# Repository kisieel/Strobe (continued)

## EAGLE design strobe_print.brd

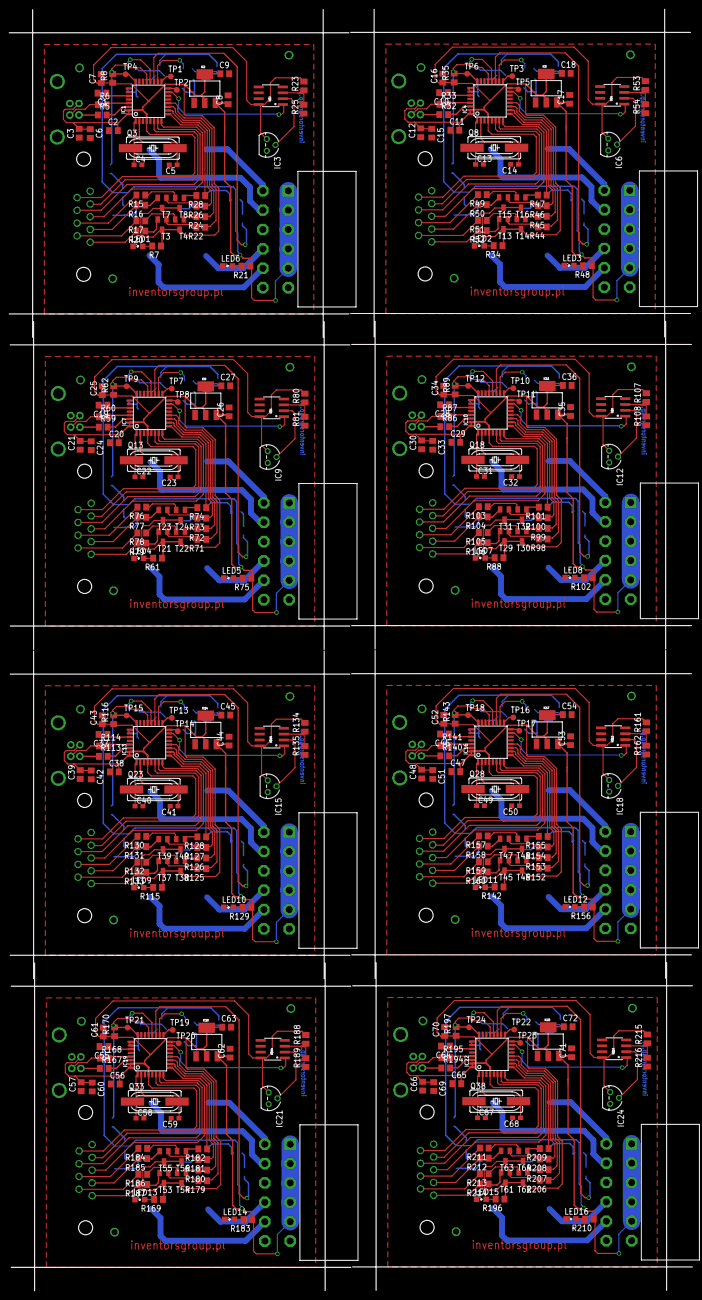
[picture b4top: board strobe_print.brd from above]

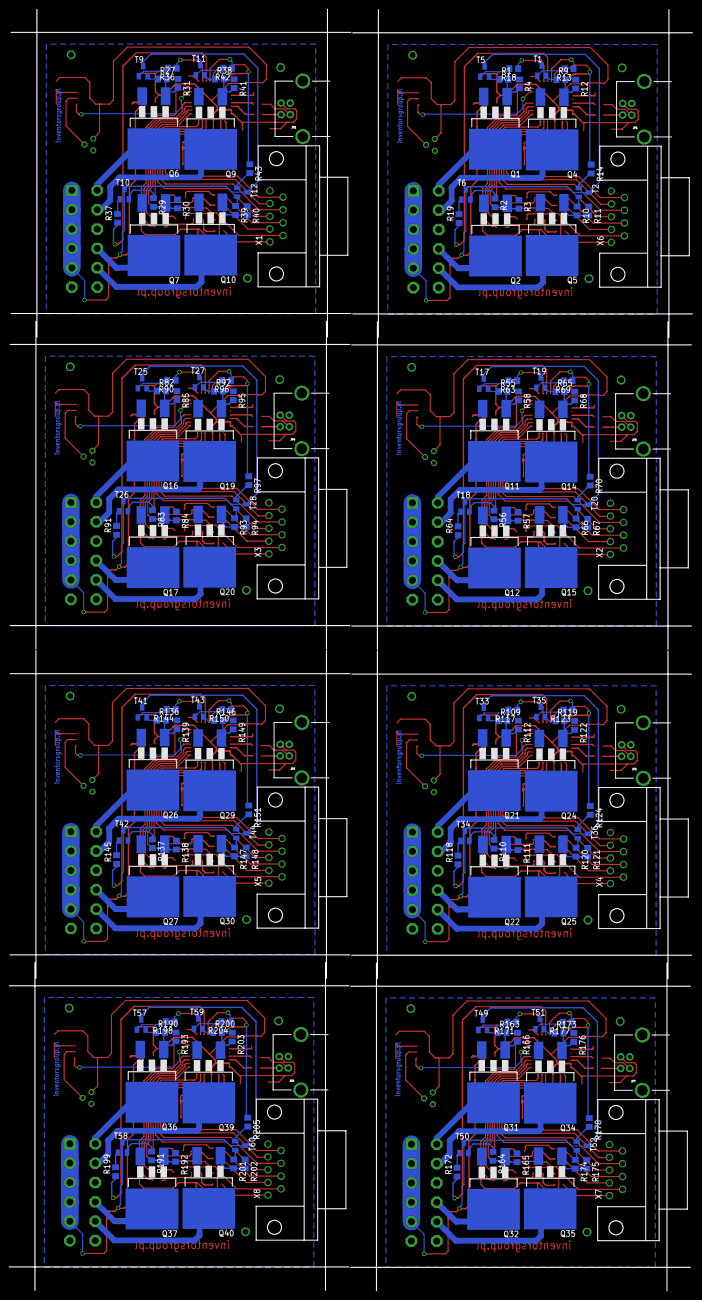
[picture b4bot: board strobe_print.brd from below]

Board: 2 copper layers, 148.1 x 277.9 mm, 488 parts (176 on the bottom side), 456 nets.

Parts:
C1, C10, C19, C28, C37, C46, C55, C64: 1uF; C0805
C2, C3, C6, C7, C8, C9, C11, C12, C15, C16, C17, C18, C20, C21, C24, C25, C26, C27, C29, C30, C33, C34, C35, C36, C38, C39, C42, C43, C44, C45, C47, C48, C51, C52, C53, C54, C56, C57, C60, C61, C62, C63, C65, C66, C69, C70, C71, C72: 100N; C0805
C4, C5, C13, C14, C22, C23, C31, C32, C40, C41, C49, C50, C58, C59, C67, C68: 22Pf; C0603
IC1, IC4, IC7, IC10, IC13, IC16, IC19, IC22: AT90USB162A; TQFP32-08
IC2, IC5, IC8, IC11, IC14, IC17, IC20, IC23: SOT223
IC3, IC6, IC9, IC12, IC15, IC18, IC21, IC24: LM35CZ; TO92
JP1, JP2, JP3, JP4, JP5, JP6, JP7, JP8: USB-B; USB-B-PTH
LED1, LED2, LED3, LED4, LED5, LED6, LED7, LED8, LED9, LED10, LED11, LED12, LED13, LED14, LED15, LED16: SML0805
Q1, Q2, Q4, Q5, Q6, Q7, Q9, Q10, Q11, Q12, Q14, Q15, Q16, Q17, Q19, Q20, Q21, Q22, Q24, Q25, Q26, Q27, Q29, Q30, Q31, Q32, Q34, Q35, Q36, Q37, Q39, Q40: IRF3704S; D2PACK
Q3, Q8, Q13, Q18, Q23, Q28, Q33, Q38: SM49
R1, R2, R3, R4, R9, R10, R11, R12, R13, R14, R15, R16, R17, R18, R19, R20, R22, R24, R26, R27, R28, R29, R30, R31, R36, R37, R38, R39, R40, R41, R42, R43, R44, R45, R46, R47, R49, R50, R51, R52, R55, R56, R57, R58, R63, R64, R65, R66, R67, R68, R69, R70, R71, R72, R73, R74, R76, R77, R78, R79, R82, R83, R84, R85, R90, R91, R92, R93, R94, R95, R96, R97, R98, R99, R100, R101, R103, R104, R105, R106, R109, R110, R111, R112, R117, R118, R119, R120, R121, R122, R123, R124, R125, R126, R127, R128, R130, R131, R132, R133, R136, R137, R138, R139, R144, R145, R146, R147, R148, R149, R150, R151, R152, R153, R154, R155, R157, R158, R159, R160, R163, R164, R165, R166, R171, R172, R173, R174, R175, R176, R177, R178, R179, R180, R181, R182, R184, R185, R186, R187, R190, R191, R192, R193, R198, R199, R200, R201, R202, R203, R204, R205, R206, R207, R208, R209, R211, R212, R213, R214: R0805
R5, R6, R32, R33, R59, R60, R86, R87, R113, R114, R140, R141, R167, R168, R194, R195: 22; R0805
R7, R21, R34, R48, R61, R75, R88, R102, R115, R129, R142, R156, R169, R183, R196, R210: 340; R0805
R8, R35, R62, R89, R116, R143, R170, R197: 10K; R0805
R23, R25, R53, R54, R80, R81, R107, R108, R134, R135, R161, R162, R188, R189, R215, R216: M0805
T1, T2, T3, T4, T5, T6, T7, T8, T9, T10, T11, T12, T13, T14, T15, T16, T17, T18, T19, T20, T21, T22, T23, T24, T25, T26, T27, T28, T29, T30, T31, T32, T33, T34, T35, T36, T37, T38, T39, T40, T41, T42, T43, T44, T45, T46, T47, T48, T49, T50, T51, T52, T53, T54, T55, T56, T57, T58, T59, T60, T61, T62, T63, T64: BC849; SOT23
TP1, TP2, TP3, TP4, TP5, TP6, TP7, TP8, TP9, TP10, TP11, TP12, TP13, TP14, TP15, TP16, TP17, TP18, TP19, TP20, TP21, TP22, TP23, TP24: TPB1,27; B1,27
U$1, U$3, U$5, U$7, U$9, U$11, U$13, U$15: MF42-10
U$2, U$4, U$6, U$8, U$10, U$12, U$14, U$16: LM393; SO08
X1, X2, X3, X4, X5, X6, X7, X8: D-SUB9-H3M09RA; H3M09RA

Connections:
5V: C2.2, C3.2, C6.1, C7.1, C9.1, IC1.4, IC1.31, IC1.32, IC2.2, IC2.4, IC3.1, JP1.VBUS, R7.1, R8.1, R23.2, T3.3, T4.3, T7.3, T8.3, U$2.8, X6.9
5V1: C11.2, C12.2, C15.1, C16.1, C18.1, IC4.4, IC4.31, IC4.32, IC5.2, IC5.4, IC6.1, JP2.VBUS, R34.1, R35.1, R53.2, T13.3, T14.3, T15.3, T16.3, U$4.8, X1.9
5V2: C20.2, C21.2, C24.1, C25.1, C27.1, IC7.4, IC7.31, IC7.32, IC8.2, IC8.4, IC9.1, JP3.VBUS, R61.1, R62.1, R80.2, T21.3, T22.3, T23.3, T24.3, U$6.8, X2.9
5V3: C29.2, C30.2, C33.1, C34.1, C36.1, IC10.4, IC10.31, IC10.32, IC11.2, IC11.4, IC12.1, JP4.VBUS, R88.1, R89.1, R107.2, T29.3, T30.3, T31.3, T32.3, U$8.8, X3.9
5V4: C38.2, C39.2, C42.1, C43.1, C45.1, IC13.4, IC13.31, IC13.32, IC14.2, IC14.4, IC15.1, JP5.VBUS, R115.1, R116.1, R134.2, T37.3, T38.3, T39.3, T40.3, U$10.8, X4.9
5V5: C47.2, C48.2, C51.1, C52.1, C54.1, IC16.4, IC16.31, IC16.32, IC17.2, IC17.4, IC18.1, JP6.VBUS, R142.1, R143.1, R161.2, T45.3, T46.3, T47.3, T48.3, U$12.8, X5.9
5V6: C56.2, C57.2, C60.1, C61.1, C63.1, IC19.4, IC19.31, IC19.32, IC20.2, IC20.4, IC21.1, JP7.VBUS, R169.1, R170.1, R188.2, T53.3, T54.3, T55.3, T56.3, U$14.8, X7.9
5V7: C65.2, C66.2, C69.1, C70.1, C72.1, IC22.4, IC22.31, IC22.32, IC23.2, IC23.4, IC24.1, JP8.VBUS, R196.1, R197.1, R215.2, T61.3, T62.3, T63.3, T64.3, U$16.8, X8.9
12V: C8.1, IC2.3, R21.1, T1.3, T2.3, T5.3, T6.3, U$1.1, U$1.2, U$1.3, U$1.4, U$1.5
12V1: C17.1, IC5.3, R48.1, T9.3, T10.3, T11.3, T12.3, U$3.1, U$3.2, U$3.3, U$3.4, U$3.5
12V2: C26.1, IC8.3, R75.1, T17.3, T18.3, T19.3, T20.3, U$5.1, U$5.2, U$5.3, U$5.4, U$5.5
12V3: C35.1, IC11.3, R102.1, T25.3, T26.3, T27.3, T28.3, U$7.1, U$7.2, U$7.3, U$7.4, U$7.5
12V4: C44.1, IC14.3, R129.1, T33.3, T34.3, T35.3, T36.3, U$9.1, U$9.2, U$9.3, U$9.4, U$9.5
12V5: C53.1, IC17.3, R156.1, T41.3, T42.3, T43.3, T44.3, U$11.1, U$11.2, U$11.3, U$11.4, U$11.5
12V6: C62.1, IC20.3, R183.1, T49.3, T50.3, T51.3, T52.3, U$13.1, U$13.2, U$13.3, U$13.4, U$13.5
12V7: C71.1, IC23.3, R210.1, T57.3, T58.3, T59.3, T60.3, U$15.1, U$15.2, U$15.3, U$15.4, U$15.5
B1: IC1.6, X6.4
B2: IC1.7, X6.8
B3: IC1.8, X6.3
B4: IC4.6, X1.4
B5: IC4.7, X1.8
B6: IC4.8, X1.3
B7: IC7.6, X2.4
B8: IC7.7, X2.8
B9: IC7.8, X2.3
B10: IC10.6, X3.4
B11: IC10.7, X3.8
B12: IC10.8, X3.3
B13: IC13.6, X4.4
B14: IC13.7, X4.8
B15: IC13.8, X4.3
B16: IC16.6, X5.4
B17: IC16.7, X5.8
B18: IC16.8, X5.3
B19: IC19.6, X7.4
B20: IC19.7, X7.8
B21: IC19.8, X7.3
B22: IC22.6, X8.4
B23: IC22.7, X8.8
B24: IC22.8, X8.3
CH1: IC1.18, R18.1
CH2: IC1.19, R19.1
CH3: IC1.20, R13.1
CH4: IC1.21, R14.1
CH5: IC4.18, R36.1
CH6: IC4.19, R37.1
CH7: IC4.20, R42.1
CH8: IC4.21, R43.1
CH9: IC7.18, R63.1
CH10: IC7.19, R64.1
CH11: IC7.20, R69.1
CH12: IC7.21, R70.1
CH13: IC10.18, R90.1
CH14: IC10.19, R91.1
CH15: IC10.20, R96.1
CH16: IC10.21, R97.1
CH17: IC13.18, R117.1
CH18: IC13.19, R118.1
CH19: IC13.20, R123.1
CH20: IC13.21, R124.1
CH21: IC16.18, R144.1
CH22: IC16.19, R145.1
CH23: IC16.20, R150.1
CH24: IC16.21, R151.1
CH25: IC19.18, R171.1
CH26: IC19.19, R172.1
CH27: IC19.20, R177.1
CH28: IC19.21, R178.1
CH29: IC22.18, R198.1
CH30: IC22.19, R199.1
CH31: IC22.20, R204.1
CH32: IC22.21, R205.1
GND: C1.2, C2.1, C3.1, C4.2, C5.2, C6.2, C7.2, C8.2, C9.2, IC1.3, IC1.28, IC2.1, IC3.3, JP1.GND, LED1.C, LED6.C, Q1.3, Q2.3, Q4.3, Q5.3, R3.1, R4.1, R11.1, R12.1, R25.1, U$1.8, U$1.11, U$1.12, U$2.4, X6.5
GND1: C10.2, C11.1, C12.1, C13.2, C14.2, C15.2, C16.2, C17.2, C18.2, IC4.3, IC4.28, IC5.1, IC6.3, JP2.GND, LED2.C, LED3.C, Q6.3, Q7.3, Q9.3, Q10.3, R30.1, R31.1, R40.1, R41.1, R54.1, U$3.8, U$3.11, U$3.12, U$4.4, X1.5
GND2: C19.2, C20.1, C21.1, C22.2, C23.2, C24.2, C25.2, C26.2, C27.2, IC7.3, IC7.28, IC8.1, IC9.3, JP3.GND, LED4.C, LED5.C, Q11.3, Q12.3, Q14.3, Q15.3, R57.1, R58.1, R67.1, R68.1, R81.1, U$5.8, U$5.11, U$5.12, U$6.4, X2.5
GND3: C28.2, C29.1, C30.1, C31.2, C32.2, C33.2, C34.2, C35.2, C36.2, IC10.3, IC10.28, IC11.1, IC12.3, JP4.GND, LED7.C, LED8.C, Q16.3, Q17.3, Q19.3, Q20.3, R84.1, R85.1, R94.1, R95.1, R108.1, U$7.8, U$7.11, U$7.12, U$8.4, X3.5
GND4: C37.2, C38.1, C39.1, C40.2, C41.2, C42.2, C43.2, C44.2, C45.2, IC13.3, IC13.28, IC14.1, IC15.3, JP5.GND, LED9.C, LED10.C, Q21.3, Q22.3, Q24.3, Q25.3, R111.1, R112.1, R121.1, R122.1, R135.1, U$9.8, U$9.11, U$9.12, U$10.4, X4.5
GND5: C46.2, C47.1, C48.1, C49.2, C50.2, C51.2, C52.2, C53.2, C54.2, IC16.3, IC16.28, IC17.1, IC18.3, JP6.GND, LED11.C, LED12.C, Q26.3, Q27.3, Q29.3, Q30.3, R138.1, R139.1, R148.1, R149.1, R162.1, U$11.8, U$11.11, U$11.12, U$12.4, X5.5
GND6: C55.2, C56.1, C57.1, C58.2, C59.2, C60.2, C61.2, C62.2, C63.2, IC19.3, IC19.28, IC20.1, IC21.3, JP7.GND, LED13.C, LED14.C, Q31.3, Q32.3, Q34.3, Q35.3, R165.1, R166.1, R175.1, R176.1, R189.1, U$13.8, U$13.11, U$13.12, U$14.4, X7.5
GND7: C64.2, C65.1, C66.1, C67.2, C68.2, C69.2, C70.2, C71.2, C72.2, IC22.3, IC22.28, IC23.1, IC24.3, JP8.GND, LED15.C, LED16.C, Q36.3, Q37.3, Q39.3, Q40.3, R192.1, R193.1, R202.1, R203.1, R216.1, U$15.8, U$15.11, U$15.12, U$16.4, X8.5
L1: Q1.2, U$1.6
L2: Q2.2, U$1.9
L3: Q4.2, U$1.7
L4: Q5.2, U$1.10
L5: Q6.2, U$3.6
L6: Q7.2, U$3.9
L7: Q9.2, U$3.7
L8: Q10.2, U$3.10
L9: Q11.2, U$5.6
L10: Q12.2, U$5.9
L11: Q14.2, U$5.7
L12: Q15.2, U$5.10
L13: Q16.2, U$7.6
L14: Q17.2, U$7.9
L15: Q19.2, U$7.7
L16: Q20.2, U$7.10
L17: Q21.2, U$9.6
L18: Q22.2, U$9.9
L19: Q24.2, U$9.7
L20: Q25.2, U$9.10
L21: Q26.2, U$11.6
L22: Q27.2, U$11.9
L23: Q29.2, U$11.7
L24: Q30.2, U$11.10
L25: Q31.2, U$13.6
L26: Q32.2, U$13.9
L27: Q34.2, U$13.7
L28: Q35.2, U$13.10
L29: Q36.2, U$15.6
L30: Q37.2, U$15.9
L31: Q39.2, U$15.7
L32: Q40.2, U$15.10
unnamed: Q1.1, R1.2, R4.2
unnamed: Q2.1, R2.2, R3.2
unnamed: IC3.2, U$2.2
unnamed: R23.1, R25.2, U$2.3
unnamed: C1.1, IC1.27
unnamed: JP1.D+, R6.1
unnamed: JP1.D-, R5.1
unnamed: IC1.30, R5.2
unnamed: IC1.29, R6.2
unnamed: LED1.A, R7.2
unnamed: Q4.1, R9.2, R12.2
unnamed: C5.1, IC1.2, Q3.2
unnamed: C4.1, IC1.1, Q3.1
unnamed: IC1.24, R8.2, TP4.TP
unnamed: Q5.1, R10.2, R11.2
unnamed: Q6.1, R27.2, R31.2
unnamed: Q7.1, R29.2, R30.2
unnamed: R9.1, T1.2
unnamed: R10.1, T2.2
unnamed: R13.2, T1.1
unnamed: R14.2, T2.1
unnamed: IC1.17, TP1.TP
unnamed: LED6.A, R21.2
unnamed: R22.2, T3.1
unnamed: IC1.16, TP2.TP
unnamed: R20.2, X6.1
unnamed: R24.2, T4.1
unnamed: R1.1, T5.2
unnamed: R2.1, T6.2
unnamed: R18.2, T5.1
unnamed: R19.2, T6.1
unnamed: C10.1, IC4.27
unnamed: R17.2, X6.6
unnamed: R26.2, T7.1
unnamed: R16.2, X6.2
unnamed: R15.2, X6.7
unnamed: R28.2, T8.1
unnamed: JP2.D+, R33.1
unnamed: JP2.D-, R32.1
unnamed: IC4.30, R32.2
unnamed: IC4.29, R33.2
unnamed: LED2.A, R34.2
unnamed: C14.1, IC4.2, Q8.2
unnamed: C13.1, IC4.1, Q8.1
unnamed: IC4.24, R35.2, TP6.TP
unnamed: R27.1, T9.2
unnamed: R29.1, T10.2
unnamed: R36.2, T9.1
unnamed: R37.2, T10.1
unnamed: Q9.1, R38.2, R41.2
unnamed: Q10.1, R39.2, R40.2
unnamed: R38.1, T11.2
unnamed: R39.1, T12.2
unnamed: R42.2, T11.1
unnamed: R43.2, T12.1
unnamed: R44.2, T13.1
unnamed: R45.2, T14.1
unnamed: R46.2, T15.1
unnamed: R47.2, T16.1
unnamed: IC4.17, TP3.TP
unnamed: IC4.16, TP5.TP
unnamed: LED3.A, R48.2
unnamed: R52.2, X1.1
unnamed: R51.2, X1.6
unnamed: R50.2, X1.2
unnamed: R49.2, X1.7
unnamed: IC6.2, U$4.2
unnamed: R53.1, R54.2, U$4.3
unnamed: Q11.1, R55.2, R58.2
unnamed: Q12.1, R56.2, R57.2
unnamed: C19.1, IC7.27
unnamed: JP3.D+, R60.1
unnamed: JP3.D-, R59.1
unnamed: IC7.30, R59.2
unnamed: IC7.29, R60.2
unnamed: LED4.A, R61.2
unnamed: C23.1, IC7.2, Q13.2
unnamed: C22.1, IC7.1, Q13.1
unnamed: IC7.24, R62.2, TP9.TP
unnamed: R55.1, T17.2
unnamed: R56.1, T18.2
unnamed: R63.2, T17.1
unnamed: R64.2, T18.1
unnamed: Q14.1, R65.2, R68.2
unnamed: Q15.1, R66.2, R67.2
unnamed: R65.1, T19.2
unnamed: R66.1, T20.2
unnamed: R69.2, T19.1
unnamed: R70.2, T20.1
unnamed: R71.2, T21.1
unnamed: R72.2, T22.1
unnamed: R73.2, T23.1
unnamed: R74.2, T24.1
unnamed: IC7.17, TP7.TP
unnamed: IC7.16, TP8.TP
unnamed: LED5.A, R75.2
unnamed: R79.2, X2.1
unnamed: R78.2, X2.6
unnamed: R77.2, X2.2
unnamed: R76.2, X2.7
unnamed: IC9.2, U$6.2
unnamed: R80.1, R81.2, U$6.3
unnamed: Q16.1, R82.2, R85.2
unnamed: Q17.1, R83.2, R84.2
unnamed: C28.1, IC10.27
unnamed: JP4.D+, R87.1
unnamed: JP4.D-, R86.1
unnamed: IC10.30, R86.2
unnamed: IC10.29, R87.2
unnamed: LED7.A, R88.2
unnamed: C32.1, IC10.2, Q18.2
unnamed: C31.1, IC10.1, Q18.1
unnamed: IC10.24, R89.2, TP12.TP
unnamed: R82.1, T25.2
unnamed: R83.1, T26.2
unnamed: R90.2, T25.1
unnamed: R91.2, T26.1
unnamed: Q19.1, R92.2, R95.2
unnamed: Q20.1, R93.2, R94.2
unnamed: R92.1, T27.2
unnamed: R93.1, T28.2
unnamed: R96.2, T27.1
unnamed: R97.2, T28.1
unnamed: R98.2, T29.1
unnamed: R99.2, T30.1
unnamed: R100.2, T31.1
unnamed: R101.2, T32.1
unnamed: IC10.17, TP10.TP
unnamed: IC10.16, TP11.TP
unnamed: LED8.A, R102.2
unnamed: R106.2, X3.1
unnamed: R105.2, X3.6
unnamed: R104.2, X3.2
unnamed: R103.2, X3.7
unnamed: IC12.2, U$8.2
unnamed: R107.1, R108.2, U$8.3
unnamed: Q21.1, R109.2, R112.2
unnamed: Q22.1, R110.2, R111.2
unnamed: C37.1, IC13.27
unnamed: JP5.D+, R114.1
unnamed: JP5.D-, R113.1
unnamed: IC13.30, R113.2
unnamed: IC13.29, R114.2
unnamed: LED9.A, R115.2
unnamed: C41.1, IC13.2, Q23.2
unnamed: C40.1, IC13.1, Q23.1
unnamed: IC13.24, R116.2, TP15.TP
unnamed: R109.1, T33.2
unnamed: R110.1, T34.2
unnamed: R117.2, T33.1
unnamed: R118.2, T34.1
unnamed: Q24.1, R119.2, R122.2
unnamed: Q25.1, R120.2, R121.2
unnamed: R119.1, T35.2
unnamed: R120.1, T36.2
unnamed: R123.2, T35.1
unnamed: R124.2, T36.1
unnamed: R125.2, T37.1
unnamed: R126.2, T38.1
unnamed: R127.2, T39.1
unnamed: R128.2, T40.1
unnamed: IC13.17, TP13.TP
unnamed: IC13.16, TP14.TP
unnamed: LED10.A, R129.2
unnamed: R133.2, X4.1
unnamed: R132.2, X4.6
unnamed: R131.2, X4.2
unnamed: R130.2, X4.7
unnamed: IC15.2, U$10.2
unnamed: R134.1, R135.2, U$10.3
unnamed: Q26.1, R136.2, R139.2
unnamed: Q27.1, R137.2, R138.2
unnamed: C46.1, IC16.27
unnamed: JP6.D+, R141.1
unnamed: JP6.D-, R140.1
unnamed: IC16.30, R140.2
unnamed: IC16.29, R141.2
unnamed: LED11.A, R142.2
unnamed: C50.1, IC16.2, Q28.2
unnamed: C49.1, IC16.1, Q28.1
unnamed: IC16.24, R143.2, TP18.TP
unnamed: R136.1, T41.2
unnamed: R137.1, T42.2
unnamed: R144.2, T41.1
unnamed: R145.2, T42.1
unnamed: Q29.1, R146.2, R149.2
unnamed: Q30.1, R147.2, R148.2
unnamed: R146.1, T43.2
unnamed: R147.1, T44.2
unnamed: R150.2, T43.1
unnamed: R151.2, T44.1
unnamed: R152.2, T45.1
unnamed: R153.2, T46.1
unnamed: R154.2, T47.1
unnamed: R155.2, T48.1
unnamed: IC16.17, TP16.TP
unnamed: IC16.16, TP17.TP
unnamed: LED12.A, R156.2
unnamed: R160.2, X5.1
unnamed: R159.2, X5.6
unnamed: R158.2, X5.2
unnamed: R157.2, X5.7
unnamed: IC18.2, U$12.2
unnamed: R161.1, R162.2, U$12.3
unnamed: Q31.1, R163.2, R166.2
unnamed: Q32.1, R164.2, R165.2
unnamed: C55.1, IC19.27
unnamed: JP7.D+, R168.1
unnamed: JP7.D-, R167.1
unnamed: IC19.30, R167.2
unnamed: IC19.29, R168.2
unnamed: LED13.A, R169.2
unnamed: C59.1, IC19.2, Q33.2
unnamed: C58.1, IC19.1, Q33.1
unnamed: IC19.24, R170.2, TP21.TP
unnamed: R163.1, T49.2
unnamed: R164.1, T50.2
unnamed: R171.2, T49.1
unnamed: R172.2, T50.1
unnamed: Q34.1, R173.2, R176.2
unnamed: Q35.1, R174.2, R175.2
unnamed: R173.1, T51.2
unnamed: R174.1, T52.2
unnamed: R177.2, T51.1
unnamed: R178.2, T52.1
unnamed: R179.2, T53.1
unnamed: R180.2, T54.1
unnamed: R181.2, T55.1
unnamed: R182.2, T56.1
unnamed: IC19.17, TP19.TP
unnamed: IC19.16, TP20.TP
unnamed: LED14.A, R183.2
unnamed: R187.2, X7.1
unnamed: R186.2, X7.6
unnamed: R185.2, X7.2
unnamed: R184.2, X7.7
unnamed: IC21.2, U$14.2
unnamed: R188.1, R189.2, U$14.3
unnamed: Q36.1, R190.2, R193.2
unnamed: Q37.1, R191.2, R192.2
unnamed: C64.1, IC22.27
unnamed: JP8.D+, R195.1
unnamed: JP8.D-, R194.1
unnamed: IC22.30, R194.2
unnamed: IC22.29, R195.2
unnamed: LED15.A, R196.2
unnamed: C68.1, IC22.2, Q38.2
unnamed: C67.1, IC22.1, Q38.1
unnamed: IC22.24, R197.2, TP24.TP
unnamed: R190.1, T57.2
unnamed: R191.1, T58.2
unnamed: R198.2, T57.1
unnamed: R199.2, T58.1
unnamed: Q39.1, R200.2, R203.2
unnamed: Q40.1, R201.2, R202.2
unnamed: R200.1, T59.2
unnamed: R201.1, T60.2
unnamed: R204.2, T59.1
unnamed: R205.2, T60.1
unnamed: R206.2, T61.1
unnamed: R207.2, T62.1
unnamed: R208.2, T63.1
unnamed: R209.2, T64.1
unnamed: IC22.17, TP22.TP
unnamed: IC22.16, TP23.TP
unnamed: LED16.A, R210.2
unnamed: R214.2, X8.1
unnamed: R213.2, X8.6
unnamed: R212.2, X8.2
unnamed: R211.2, X8.7
unnamed: IC24.2, U$16.2
unnamed: R215.1, R216.2, U$16.3
O1: R20.1, T3.2
O2: R17.1, T4.2
O3: R16.1, T7.2
O4: R15.1, T8.2
O5: R49.1, T16.2
O6: R50.1, T15.2
O7: R51.1, T14.2
O8: R52.1, T13.2
O9: R76.1, T24.2
O10: R77.1, T23.2
O11: R78.1, T22.2
O12: R79.1, T21.2
O13: R103.1, T32.2
O14: R104.1, T31.2
O15: R105.1, T30.2
O16: R106.1, T29.2
O17: R130.1, T40.2
O18: R131.1, T39.2
O19: R132.1, T38.2
O20: R133.1, T37.2
O21: R157.1, T48.2
O22: R158.1, T47.2
O23: R159.1, T46.2
O24: R160.1, T45.2
O25: R184.1, T56.2
O26: R185.1, T55.2
O27: R186.1, T54.2
O28: R187.1, T53.2
O29: R211.1, T64.2
O30: R212.1, T63.2
O31: R213.1, T62.2
O32: R214.1, T61.2
T1: IC1.12, R22.1
T2: IC1.11, R24.1
T3: IC1.10, R26.1
T4: IC1.9, R28.1
T6: IC4.12, R44.1
T7: IC4.11, R45.1
T8: IC4.10, R46.1
T9: IC4.9, R47.1
T11: IC7.12, R71.1
T12: IC7.11, R72.1
T13: IC7.10, R73.1
T14: IC7.9, R74.1
T16: IC10.12, R98.1
T17: IC10.11, R99.1
T18: IC10.10, R100.1
T19: IC10.9, R101.1
T21: IC13.12, R125.1
T22: IC13.11, R126.1
T23: IC13.10, R127.1
T24: IC13.9, R128.1
T26: IC16.12, R152.1
T27: IC16.11, R153.1
T28: IC16.10, R154.1
T29: IC16.9, R155.1
T31: IC19.12, R179.1
T32: IC19.11, R180.1
T33: IC19.10, R181.1
T34: IC19.9, R182.1
T36: IC22.12, R206.1
T37: IC22.11, R207.1
T38: IC22.10, R208.1
T39: IC22.9, R209.1
TEMP: IC1.15, U$2.1
TEMP1: IC4.15, U$4.1
TEMP2: IC7.15, U$6.1
TEMP3: IC10.15, U$8.1
TEMP4: IC13.15, U$10.1
TEMP5: IC16.15, U$12.1
TEMP6: IC19.15, U$14.1
TEMP7: IC22.15, U$16.1

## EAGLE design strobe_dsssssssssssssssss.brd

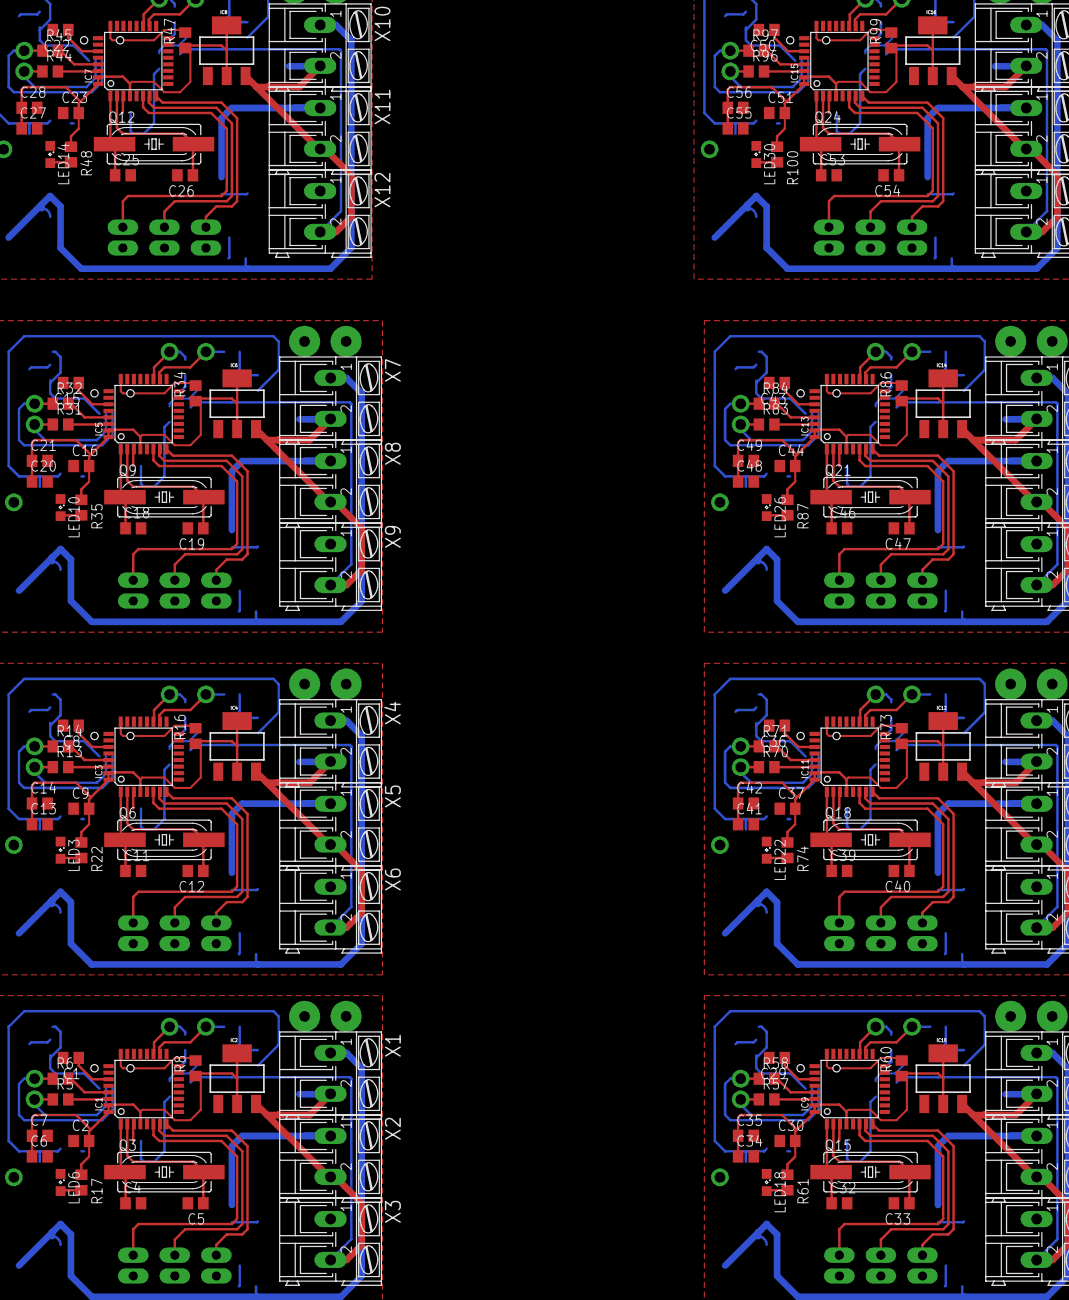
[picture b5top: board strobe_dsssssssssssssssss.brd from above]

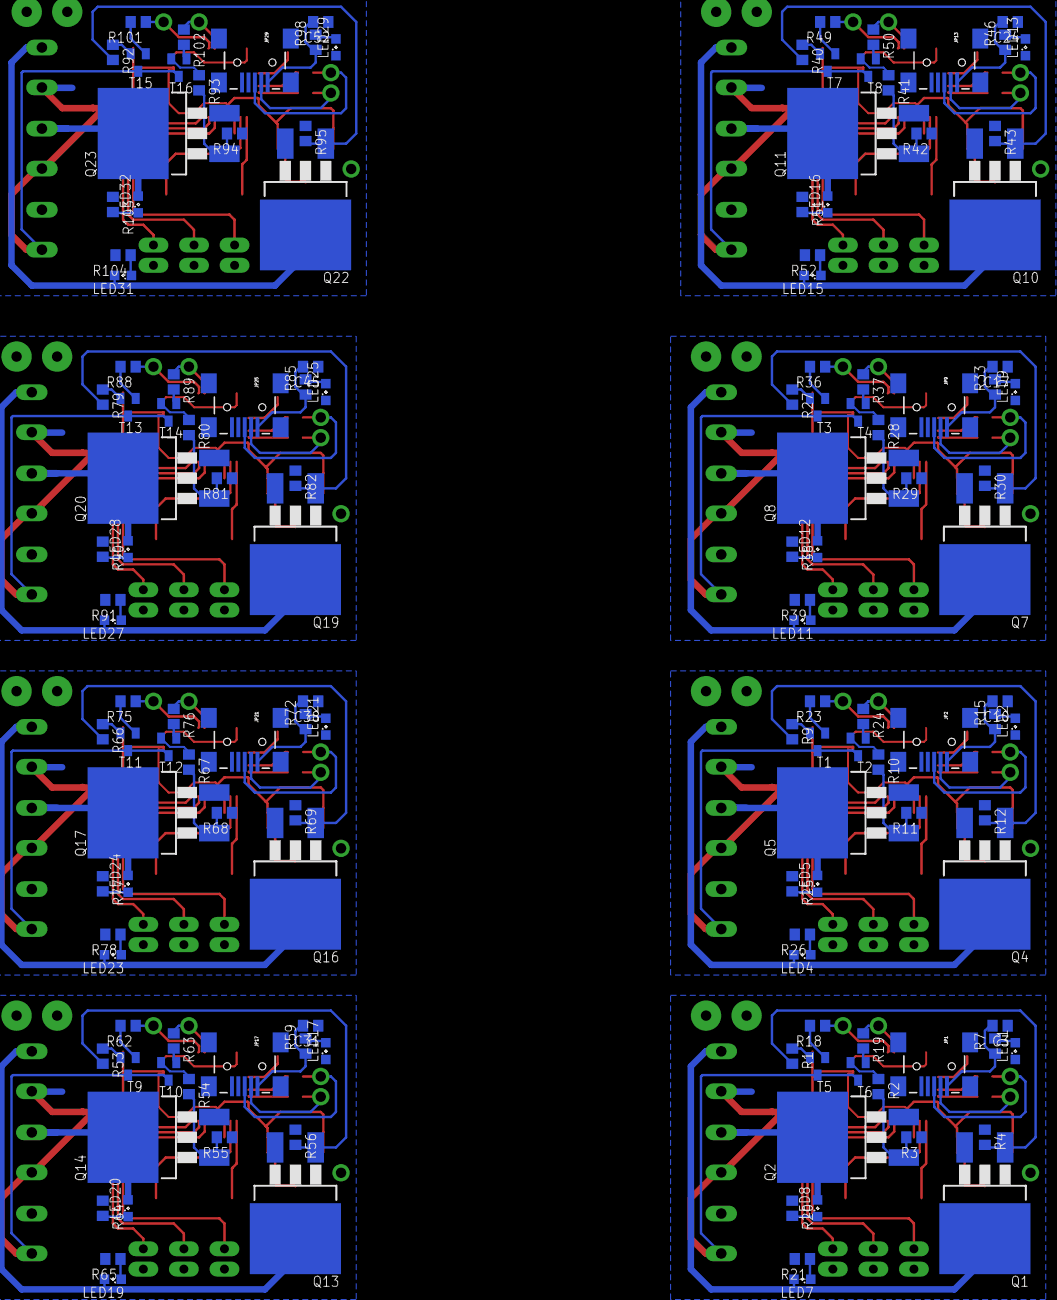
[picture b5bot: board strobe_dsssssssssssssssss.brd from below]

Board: 2 copper layers, 305 parts (144 on the bottom side), 232 nets.

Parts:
C1, C8, C15, C22, C29, C36, C43, C50: 1uF; C0805
C2, C3, C6, C7, C9, C10, C13, C14, C16, C17, C20, C21, C23, C24, C27, C28, C30, C31, C34, C35, C37, C38, C41, C42, C44, C45, C48, C49, C51, C52, C55, C56: 100N; C0805
C4, C5, C11, C12, C18, C19, C25, C26, C32, C33, C39, C40, C46, C47, C53, C54: 22Pf; C0805
E$1: A4P-LOC
IC1, IC3, IC5, IC7, IC9, IC11, IC13, IC15: AT90USB162A; TQFP32-08
IC2, IC4, IC6, IC8, IC10, IC12, IC14, IC16: SOT223
JP1, JP2, JP9, JP13, JP17, JP21, JP25, JP29: USBSMD; USB-MINIB
JP3, JP4, JP5, JP6, JP7, JP8, JP10, JP11, JP12, JP14, JP15, JP16, JP18, JP19, JP20, JP22, JP23, JP24, JP26, JP27, JP28, JP30, JP31, JP32: 1X02_LONGPADS
LED1, LED2, LED3, LED4, LED5, LED6, LED7, LED8, LED9, LED10, LED11, LED12, LED13, LED14, LED15, LED16, LED17, LED18, LED19, LED20, LED21, LED22, LED23, LED24, LED25, LED26, LED27, LED28, LED29, LED30, LED31, LED32: SML0805
Q1, Q2, Q4, Q5, Q7, Q8, Q10, Q11, Q13, Q14, Q16, Q17, Q19, Q20, Q22, Q23: IRF3704S; D2PACK
Q3, Q6, Q9, Q12, Q15, Q18, Q21, Q24: SM49
R1, R2, R3, R4, R9, R10, R11, R12, R18, R19, R20, R21, R23, R24, R25, R26, R27, R28, R29, R30, R36, R37, R38, R39, R40, R41, R42, R43, R49, R50, R51, R52, R53, R54, R55, R56, R62, R63, R64, R65, R66, R67, R68, R69, R75, R76, R77, R78, R79, R80, R81, R82, R88, R89, R90, R91, R92, R93, R94, R95, R101, R102, R103, R104: R0805
R5, R6, R13, R14, R31, R32, R44, R45, R57, R58, R70, R71, R83, R84, R96, R97: 22; R0805
R7, R15, R17, R22, R33, R35, R46, R48, R59, R61, R72, R74, R85, R87, R98, R100: 340; R0805
R8, R16, R34, R47, R60, R73, R86, R99: 10K; R0805
T1, T2, T3, T4, T5, T6, T7, T8, T9, T10, T11, T12, T13, T14, T15, T16: BC849; SOT23
X1, X2, X3, X4, X5, X6, X7, X8, X9, X10, X11, X12, X13, X14, X15, X16, X17, X18, X19, X20, X21, X22, X23, X24: AK300/2

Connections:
5V: C2.2, C6.1, C7.1, IC1.4, IC1.31, IC1.32, IC2.2, IC2.4, R8.1, R17.1
5V1: C9.2, C13.1, C14.1, IC3.4, IC3.31, IC3.32, IC4.2, IC4.4, R16.1, R22.1
5V2: C16.2, C20.1, C21.1, IC5.4, IC5.31, IC5.32, IC6.2, IC6.4, R34.1, R35.1
5V3: C23.2, C27.1, C28.1, IC7.4, IC7.31, IC7.32, IC8.2, IC8.4, R47.1, R48.1
5V4: C30.2, C34.1, C35.1, IC9.4, IC9.31, IC9.32, IC10.2, IC10.4, R60.1, R61.1
5V5: C37.2, C41.1, C42.1, IC11.4, IC11.31, IC11.32, IC12.2, IC12.4, R73.1, R74.1
5V6: C44.2, C48.1, C49.1, IC13.4, IC13.31, IC13.32, IC14.2, IC14.4, R86.1, R87.1
5V7: C51.2, C55.1, C56.1, IC15.4, IC15.31, IC15.32, IC16.2, IC16.4, R99.1, R100.1
12V: IC2.3, T5.3, T6.3, X1.2, X2.2, X3.2
12V1: IC4.3, T1.3, T2.3, X4.2, X5.2, X6.2
12V2: IC6.3, T3.3, T4.3, X7.2, X8.2, X9.2
12V3: IC8.3, T7.3, T8.3, X10.2, X11.2, X12.2
12V4: IC10.3, T9.3, T10.3, X13.2, X14.2, X15.2
12V5: IC12.3, T11.3, T12.3, X16.2, X17.2, X18.2
12V6: IC14.3, T13.3, T14.3, X19.2, X20.2, X21.2
12V7: IC16.3, T15.3, T16.3, X22.2, X23.2, X24.2
B1: IC1.6, JP4.1
B2: IC1.7, JP5.1
B3: IC1.8, JP7.1
B4: IC3.6, JP3.1
B5: IC3.7, JP6.1
B6: IC3.8, JP8.1
B7: IC5.6, JP10.1
B8: IC5.7, JP11.1
B9: IC5.8, JP12.1
B10: IC7.6, JP14.1
B11: IC7.7, JP15.1
B12: IC7.8, JP16.1
B13: IC9.6, JP18.1
B14: IC9.7, JP19.1
B15: IC9.8, JP20.1
B16: IC11.6, JP22.1
B17: IC11.7, JP23.1
B18: IC11.8, JP24.1
B19: IC13.6, JP26.1
B20: IC13.7, JP27.1
B21: IC13.8, JP28.1
B22: IC15.6, JP30.1
B23: IC15.7, JP31.1
B24: IC15.8, JP32.1
CH1: IC1.18, R18.1
CH2: IC1.19, R19.1
CH3: IC3.18, R23.1
CH4: IC3.19, R24.1
CH5: IC5.18, R36.1
CH6: IC5.19, R37.1
CH7: IC7.18, R49.1
CH8: IC7.19, R50.1
CH9: IC9.18, R62.1
CH10: IC9.19, R63.1
CH11: IC11.18, R75.1
CH12: IC11.19, R76.1
CH13: IC13.18, R88.1
CH14: IC13.19, R89.1
CH15: IC15.18, R101.1
CH16: IC15.19, R102.1
GND: C2.1, C3.1, C6.2, C7.2, IC1.3, IC1.28, IC2.1, JP1.GND, JP4.2, JP5.2, JP7.2, LED1.C, LED6.C, Q1.3, Q2.3, R3.1, R4.1, R20.1, R21.2, X3.1
GND1: C9.1, C10.1, C13.2, C14.2, IC3.3, IC3.28, IC4.1, JP2.GND, JP3.2, JP6.2, JP8.2, LED2.C, LED3.C, Q4.3, Q5.3, R11.1, R12.1, R25.1, R26.2, X6.1
GND2: C16.1, C17.1, C20.2, C21.2, IC5.3, IC5.28, IC6.1, JP9.GND, JP10.2, JP11.2, JP12.2, LED9.C, LED10.C, Q7.3, Q8.3, R29.1, R30.1, R38.1, R39.2, X9.1
GND3: C23.1, C24.1, C27.2, C28.2, IC7.3, IC7.28, IC8.1, JP13.GND, JP14.2, JP15.2, JP16.2, LED13.C, LED14.C, Q10.3, Q11.3, R42.1, R43.1, R51.1, R52.2, X12.1
GND4: C30.1, C31.1, C34.2, C35.2, IC9.3, IC9.28, IC10.1, JP17.GND, JP18.2, JP19.2, JP20.2, LED17.C, LED18.C, Q13.3, Q14.3, R55.1, R56.1, R64.1, R65.2, X15.1
GND5: C37.1, C38.1, C41.2, C42.2, IC11.3, IC11.28, IC12.1, JP21.GND, JP22.2, JP23.2, JP24.2, LED21.C, LED22.C, Q16.3, Q17.3, R68.1, R69.1, R77.1, R78.2, X18.1
GND6: C44.1, C45.1, C48.2, C49.2, IC13.3, IC13.28, IC14.1, JP25.GND, JP26.2, JP27.2, JP28.2, LED25.C, LED26.C, Q19.3, Q20.3, R81.1, R82.1, R90.1, R91.2, X21.1
GND7: C51.1, C52.1, C55.2, C56.2, IC15.3, IC15.28, IC16.1, JP29.GND, JP30.2, JP31.2, JP32.2, LED29.C, LED30.C, Q22.3, Q23.3, R94.1, R95.1, R103.1, R104.2, X24.1
unnamed: Q1.1, R1.2, R4.2
unnamed: Q2.1, R2.2, R3.2
unnamed: LED7.A, Q1.2, X1.1
unnamed: LED8.A, Q2.2, X2.1
unnamed: C1.1, IC1.27
unnamed: JP1.D+, R6.1
unnamed: JP1.D-, R5.1
unnamed: IC1.30, R5.2
unnamed: IC1.29, R6.2
unnamed: LED1.A, R7.2
unnamed: C3.2, JP1.VBUS, R7.1
unnamed: C5.1, IC1.2, Q3.2
unnamed: C4.1, IC1.1, Q3.1
unnamed: IC1.24, R8.2
unnamed: Q4.1, R9.2, R12.2
unnamed: Q5.1, R10.2, R11.2
unnamed: LED4.A, Q4.2, X4.1
unnamed: LED5.A, Q5.2, X5.1
unnamed: C8.1, IC3.27
unnamed: JP2.D+, R14.1
unnamed: JP2.D-, R13.1
unnamed: IC3.30, R13.2
unnamed: IC3.29, R14.2
unnamed: C10.2, JP2.VBUS, R15.1
unnamed: LED6.A, R17.2
unnamed: R1.1, T5.2
unnamed: R2.1, T6.2
unnamed: R18.2, T5.1
unnamed: R19.2, T6.1
unnamed: LED8.C, R20.2
unnamed: LED7.C, R21.1
unnamed: LED2.A, R15.2
unnamed: C12.1, IC3.2, Q6.2
unnamed: C11.1, IC3.1, Q6.1
unnamed: IC3.24, R16.2
unnamed: LED3.A, R22.2
unnamed: R9.1, T1.2
unnamed: R10.1, T2.2
unnamed: R23.2, T1.1
unnamed: R24.2, T2.1
unnamed: LED5.C, R25.2
unnamed: LED4.C, R26.1
unnamed: Q7.1, R27.2, R30.2
unnamed: Q8.1, R28.2, R29.2
unnamed: LED11.A, Q7.2, X7.1
unnamed: LED12.A, Q8.2, X8.1
unnamed: C15.1, IC5.27
unnamed: JP9.D+, R32.1
unnamed: JP9.D-, R31.1
unnamed: IC5.30, R31.2
unnamed: IC5.29, R32.2
unnamed: C17.2, JP9.VBUS, R33.1
unnamed: LED9.A, R33.2
unnamed: C19.1, IC5.2, Q9.2
unnamed: C18.1, IC5.1, Q9.1
unnamed: IC5.24, R34.2
unnamed: LED10.A, R35.2
unnamed: R27.1, T3.2
unnamed: R28.1, T4.2
unnamed: R36.2, T3.1
unnamed: R37.2, T4.1
unnamed: LED12.C, R38.2
unnamed: LED11.C, R39.1
unnamed: Q10.1, R40.2, R43.2
unnamed: Q11.1, R41.2, R42.2
unnamed: LED15.A, Q10.2, X10.1
unnamed: LED16.A, Q11.2, X11.1
unnamed: C22.1, IC7.27
unnamed: JP13.D+, R45.1
unnamed: JP13.D-, R44.1
unnamed: IC7.30, R44.2
unnamed: IC7.29, R45.2
unnamed: C24.2, JP13.VBUS, R46.1
unnamed: LED13.A, R46.2
unnamed: C26.1, IC7.2, Q12.2
unnamed: C25.1, IC7.1, Q12.1
unnamed: IC7.24, R47.2
unnamed: LED14.A, R48.2
unnamed: R40.1, T7.2
unnamed: R41.1, T8.2
unnamed: R49.2, T7.1
unnamed: R50.2, T8.1
unnamed: LED16.C, R51.2
unnamed: LED15.C, R52.1
unnamed: Q13.1, R53.2, R56.2
unnamed: Q14.1, R54.2, R55.2
unnamed: LED19.A, Q13.2, X13.1
unnamed: LED20.A, Q14.2, X14.1
unnamed: C29.1, IC9.27
unnamed: JP17.D+, R58.1
unnamed: JP17.D-, R57.1
unnamed: IC9.30, R57.2
unnamed: IC9.29, R58.2
unnamed: C31.2, JP17.VBUS, R59.1
unnamed: LED17.A, R59.2
unnamed: C33.1, IC9.2, Q15.2
unnamed: C32.1, IC9.1, Q15.1
unnamed: IC9.24, R60.2
unnamed: LED18.A, R61.2
unnamed: R53.1, T9.2
unnamed: R54.1, T10.2
unnamed: R62.2, T9.1
unnamed: R63.2, T10.1
unnamed: LED20.C, R64.2
unnamed: LED19.C, R65.1
unnamed: Q16.1, R66.2, R69.2
unnamed: Q17.1, R67.2, R68.2
unnamed: LED23.A, Q16.2, X16.1
unnamed: LED24.A, Q17.2, X17.1
unnamed: C36.1, IC11.27
unnamed: JP21.D+, R71.1
unnamed: JP21.D-, R70.1
unnamed: IC11.30, R70.2
unnamed: IC11.29, R71.2
unnamed: C38.2, JP21.VBUS, R72.1
unnamed: LED21.A, R72.2
unnamed: C40.1, IC11.2, Q18.2
unnamed: C39.1, IC11.1, Q18.1
unnamed: IC11.24, R73.2
unnamed: LED22.A, R74.2
unnamed: R66.1, T11.2
unnamed: R67.1, T12.2
unnamed: R75.2, T11.1
unnamed: R76.2, T12.1
unnamed: LED24.C, R77.2
unnamed: LED23.C, R78.1
unnamed: Q19.1, R79.2, R82.2
unnamed: Q20.1, R80.2, R81.2
unnamed: LED27.A, Q19.2, X19.1
unnamed: LED28.A, Q20.2, X20.1
unnamed: C43.1, IC13.27
unnamed: JP25.D+, R84.1
unnamed: JP25.D-, R83.1
unnamed: IC13.30, R83.2
unnamed: IC13.29, R84.2
unnamed: C45.2, JP25.VBUS, R85.1
unnamed: LED25.A, R85.2
unnamed: C47.1, IC13.2, Q21.2
unnamed: C46.1, IC13.1, Q21.1
unnamed: IC13.24, R86.2
unnamed: LED26.A, R87.2
unnamed: R79.1, T13.2
unnamed: R80.1, T14.2
unnamed: R88.2, T13.1
unnamed: R89.2, T14.1
unnamed: LED28.C, R90.2
unnamed: LED27.C, R91.1
unnamed: Q22.1, R92.2, R95.2
unnamed: Q23.1, R93.2, R94.2
unnamed: LED31.A, Q22.2, X22.1
unnamed: LED32.A, Q23.2, X23.1
unnamed: C50.1, IC15.27
unnamed: JP29.D+, R97.1
unnamed: JP29.D-, R96.1
unnamed: IC15.30, R96.2
unnamed: IC15.29, R97.2
unnamed: C52.2, JP29.VBUS, R98.1
unnamed: LED29.A, R98.2
unnamed: C54.1, IC15.2, Q24.2
unnamed: C53.1, IC15.1, Q24.1
unnamed: IC15.24, R99.2
unnamed: LED30.A, R100.2
unnamed: R92.1, T15.2
unnamed: R93.1, T16.2
unnamed: R101.2, T15.1
unnamed: R102.2, T16.1
unnamed: LED32.C, R103.2
unnamed: LED31.C, R104.1

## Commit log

2013-05-29 Scheme + Brd
    Beta
2013-05-29 Dobule sided board
2013-05-30 poprawki
2013-07-01 Poprawki Schematów
2013-07-01 Kod mikroporcesora
    Bez obsługi przełączników
2013-07-01 apka na kompa
2013-07-01 Dobry kodzik
2013-07-01 mała poprawka
2013-07-01 wysyłanie danych
2013-07-01 small fix
2013-07-15 Nowa płytka
    4 lampy + RJ45
2013-07-17 board fix
2013-07-21 PCB extreme makeover
2013-08-13 Close-to-final version of board
2013-08-13 Scripts
2013-08-14 bezpiecznik out
2013-08-15 dodany reset na goldpinach, poprawka przelotki
2013-08-15 fixes + expander
2013-08-15 Protective diodes added in expander
